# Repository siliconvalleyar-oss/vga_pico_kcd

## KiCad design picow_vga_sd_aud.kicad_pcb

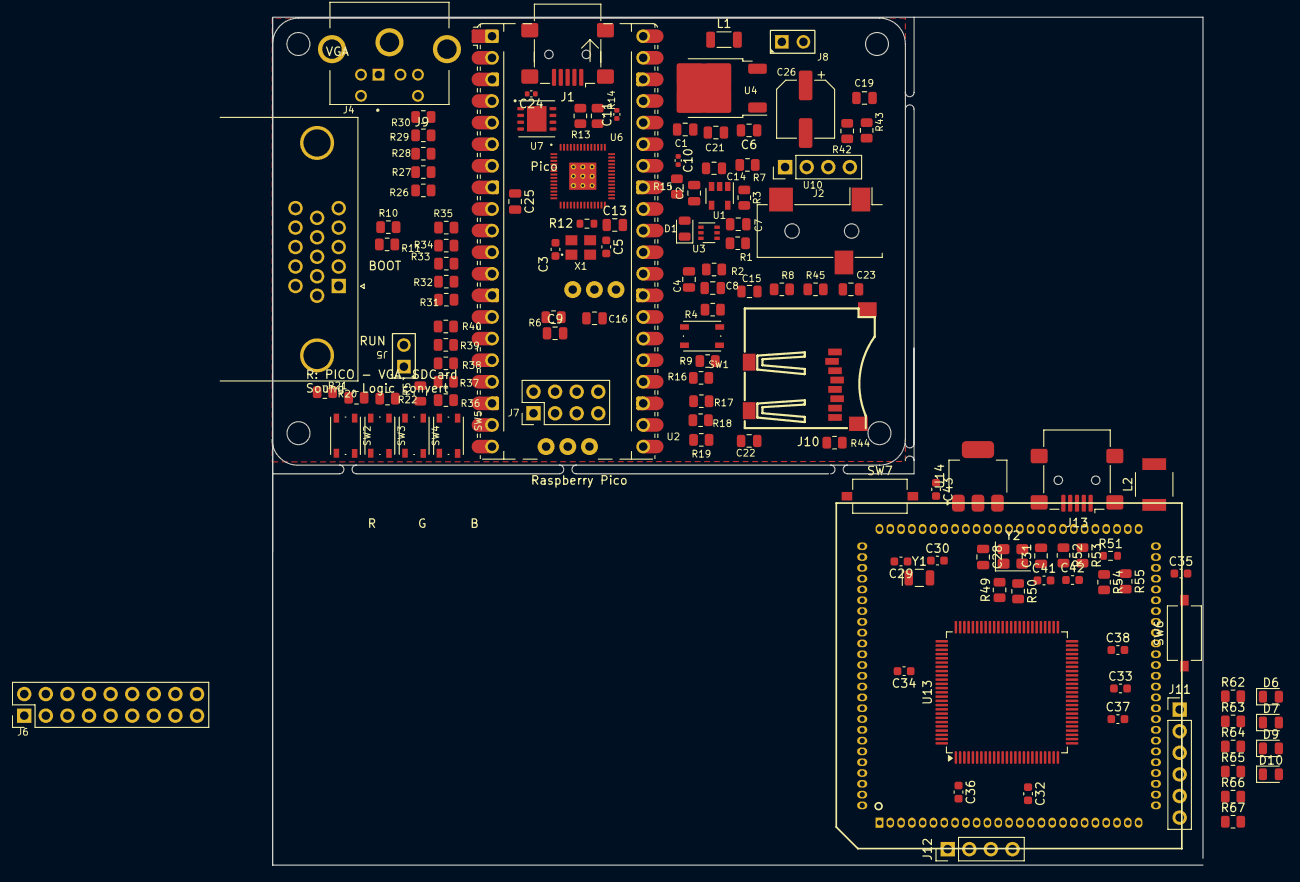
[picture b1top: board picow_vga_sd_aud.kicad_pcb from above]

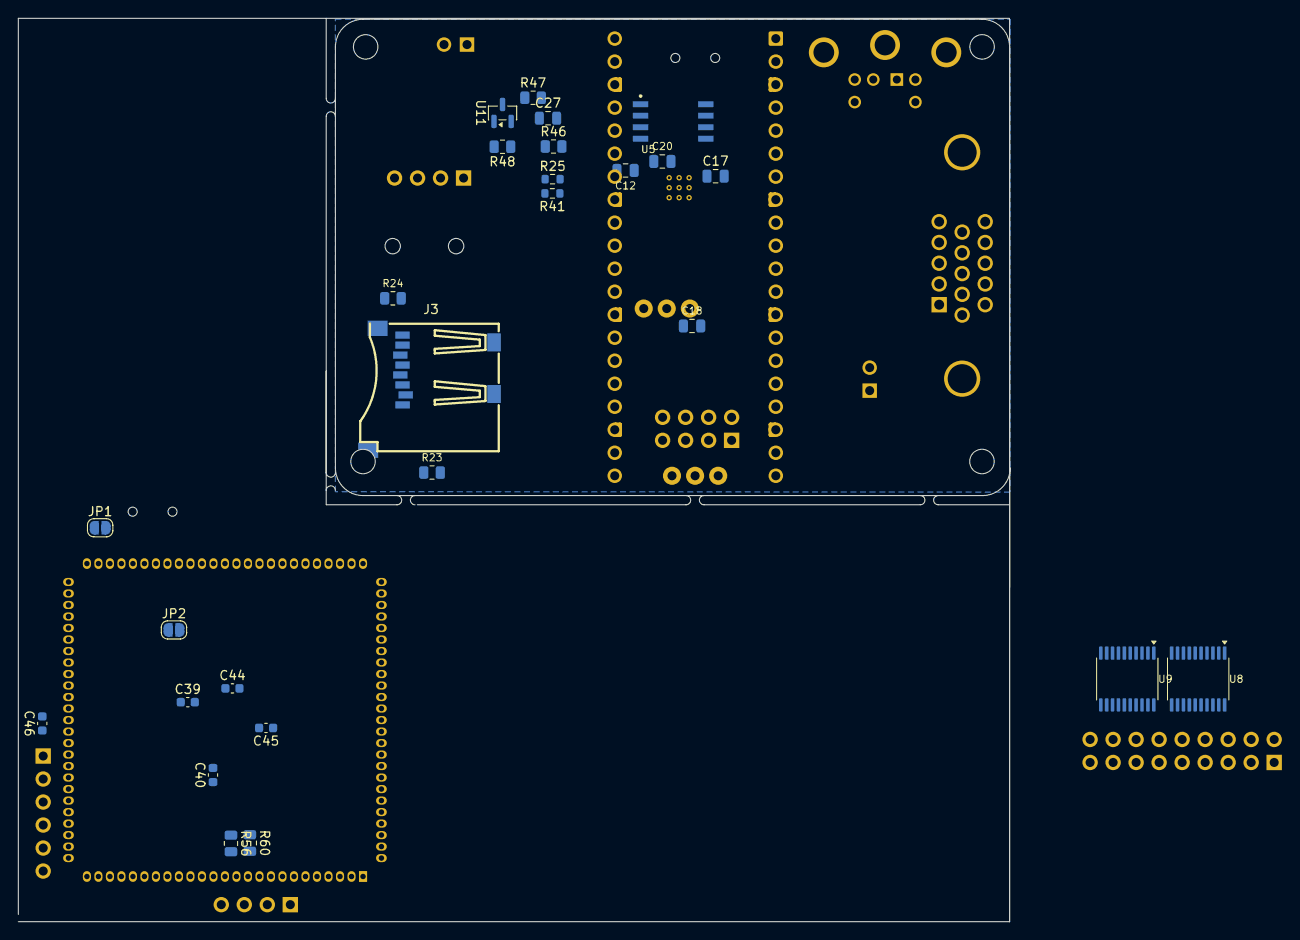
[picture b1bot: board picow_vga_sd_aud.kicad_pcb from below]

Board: 2 copper layers, 109.5 x 99.7 mm, 159 parts (26 on the bottom side), 191 nets, no tracks yet.

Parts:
C1, C2, C13, C17, C27: 1u; C_0805_2012Metric
C3, C5, C29, C30: 15p; C_0603_1608Metric
C4, C7, C8, C12, C16, C18, C20, C21, C22, C23: 100n; C_0805_2012Metric
C6, C9, C19, C25: 10u; C_0805_2012Metric
C10, C11, C24: 100n; C_0402_1005Metric
C14, C15: 47u; C_0805_2012Metric
C26: C_Polarized; CP_Elec_6.3x5.9
C28, C31: 15p; C_0805_2012Metric
C32, C36, C37, C38, C39, C40, C41, C42, C44, C45, C46: 100nf; C_0603_1608Metric
C33, C34: 100; C_0603_1608Metric
C35, C43: 4.7uf; C_0603_1608Metric
D1: LED; LED_0805_2012Metric
D6, D7, D9, D10: LED; D_0805_2012Metric
H1, H2, H3, H4: MountingHole; MountingHole_2.7mm_M2.5
J1: U-M-M5SS-W-2; USB_Mini-B_Lumberg_2486_01_Horizontal
J2: PJ-320BSurface Mount; CUI_SJ-3523-audio-jack
J3, J10: TF-001B
J4: L77HDE15SD1CH4F; DSUB-15-L77HDE15SD1CH4F
J5, J8: TSW-102-07-G-S; samtec_tsw-102-07-g-s
J6: Conn_01x18_Pin; PinHeader_2x09_P2.54mm_Vertical
J7: Conn_02x03_Odd_Even; PinHeader_2x04_P2.54mm_Vertical
J9: Mini-DIN-6; TE_5749180-1
J11: icd; PinHeader_1x06_P2.54mm_Vertical
J12: OLED SSD1306; PinHeader_1x04_P2.54mm_Vertical
J13: USB_A; USB_Mini-B_Lumberg_2486_01_Horizontal
JP1: SolderJumper-2_P1.3mm_Open_RoundedPad1.0x1.5mm
JP2: usb_on; SolderJumper-2_P1.3mm_Open_RoundedPad1.0x1.5mm
L1: 100uH; L_1206_3216Metric
L2: L; L_Neosid_Ms50
R1, R2: 220; R_0805_2012Metric
R3, R4, R54, R55: 100; R_0805_2012Metric
R5, R20, R21, R22, R27, R32, R37, R46, R47, R48: 1k; R_0805_2012Metric
R6, R23, R24: 10k; R_0805_2012Metric
R7, R8, R15: 1.8K; R_0805_2012Metric
R9: DNF; R_0805_2012Metric
R10, R11: 47; R_0805_2012Metric
R12: 1k; R_0603_1608Metric
R13, R14: 27; R_0805_2012Metric
R16, R17, R18, R19, R42, R43, R44, R45, R56, R60, R62, R63, R64, R65, R66, R67: 2k2; R_0805_2012Metric
R25: 10k; R_0603_1608Metric
R26, R31, R36: 499; R_0805_2012Metric
R28, R33, R38: 2k; R_0805_2012Metric
R29, R34, R39: 4.02k; R_0805_2012Metric
R30, R35, R40: 8.06k; R_0805_2012Metric
R41: 1K; R_0603_1608Metric
R49: 1K; R_0805_2012Metric
R50: 1M; R_0805_2012Metric
R51: 0; R_0603_1608Metric
R52, R53: 0; R_0805_2012Metric
SW1, SW2, SW3, SW4, SW5: SKRPACE010; SW_Push_1P1T_NO_Vertical_Wuerth_434133025816
SW6, SW7: K2-1107ST-A4SW-06; SW_Tactile_SPST_NO_Straight_CK_PTS636Sx25SMTRLFS
U1: TLV70033_SOT23-5; SOT-23-5
U2: PicoW; RaspberryPi_Pico
U3: NC7WZ16P6X; SOT-363_SC-70-6
U4: LM1117DT-3.3/NOPB; TO-252-2
U5: W25Q128JVSIQ; generic_soic127p790x195-8
U6: RP2040; rpi_rp2040_vias
U7: W25Q64JVXGIM; Winbond_XSON-8-1EP_4x4mm_P0.8mm_EP2.3x3.0mm
U8, U9: TXS0108; TSSOP-20_4.4x6.5mm_P0.65mm
U10: ER_OLEDM0.91_1x-I2C; PinHeader_1x04_P2.54mm_Vertical
U11: TL431DBZ; SOT-23
U12: PIC32MX795F512L-80x-PF; MA240011_Socket_TQFP100_100pin
U13: PIC32MX795F512L-80I_PF; TQFP-100_14x14mm_P0.5mm
U14: LM1117MDT-3_3_TR; SOT-223-3_TabPin2
X1: 12MHz; generic_xtalcc320x250x80-4
Y1: Crystal_Small; Crystal_SMD_EuroQuartz_EQ161-2Pin_3.2x1.5mm
Y2: 8MHz SMD crystal oscillator ±10ppm ±30ppm SMD3225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; Crystal_SMD_3225-4Pin_3.2x2.5mm

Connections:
+1V1: C11.1, C12.1, C13.1, U6.23 (DVDD), U6.45 (VREG_VOUT), U6.50 (DVDD)
+3.3VA: C2.1, C4.1, U1.5 (OUT), U3.5 (VCC)
+3V: C32.1, C33.1, C36.1, C37.1, C38.1, C39.1, C40.1, C41.1, C43.1, C44.1, C45.1, C46.1, J11.2, JP2.2 (B), U12.2 (VDD), U12.16 (VDD), U12.30 (AVDD), U12.37 (VDD), U12.46 (VDD), U12.55 (VUSB3V3), U12.62 (VDD), U12.86 (VDD), U13.2 (VDD), U13.16 (VDD), U13.37 (VDD), U13.46 (VDD), U13.62 (VDD), U13.86 (VDD), U14.2 (VOUT)
+3V3: C9.1, C10.1, C16.1, C17.1, C18.1, C19.1, C20.1, C21.1, C22.1, C23.1, C24.1, C25.1, C26.1, J3.4 (VDD), J10.4 (VDD), J12.2, R6.1, R16.2, R17.2, R18.2, R19.2, R23.2, R24.2, R25.1, R42.2, R43.2, R44.1, R45.2, R48.1, R56.1, R60.1, SW2.1, SW3.1, SW4.1, U2.36 (3V3), U4.2 (OUT), U5.8 (VCC), U6.1 (IOVDD), U6.10 (IOVDD), U6.22 (IOVDD), U6.33 (IOVDD), U6.42 (IOVDD), U6.43 (ADC_AVDD), U6.44 (VREG_IN), U6.48 (USB_VDD), U6.49 (IOVDD), U7.8 (VCC), U8.1 (VCCA), U9.1 (VCCA), U10.2 (VCC), U13.30 (AVDD)
+5V: C35.2, J13.1 (VBUS), L2.1
/GPIO0: R20.1, R30.2, U2.1 (GPIO0), U6.2 (GPIO0)
/GPIO1: R29.2, U2.2 (GPIO1), U6.3 (GPIO1)
/GPIO2: R28.2, U2.4 (GPIO2), U6.4 (GPIO2)
/GPIO3: R27.2, U2.5 (GPIO3), U6.5 (GPIO3)
/GPIO4: R26.2, U2.6 (GPIO4), U6.6 (GPIO4)
/GPIO5: J3.5 (CLK), J10.2 (DAT3/CD), R9.2, R16.1, U2.7 (GPIO5), U6.7 (GPIO5)
/GPIO6: R21.1, R35.2, U2.9 (GPIO6), U6.8 (GPIO6)
/GPIO7: R34.2, U2.10 (GPIO7), U6.9 (GPIO7)
/GPIO8: R33.2, U2.11 (GPIO8), U6.11 (GPIO8)
/GPIO9: R32.2, U2.12 (GPIO9), U6.12 (GPIO9)
/GPIO10: R31.2, U2.14 (GPIO10), U6.13 (GPIO10)
/GPIO11: R22.1, R40.2, U2.15 (GPIO11), U6.14 (GPIO11)
/GPIO12: R39.2, U2.16 (GPIO12), U6.15 (GPIO12)
/GPIO13: R38.2, U2.17 (GPIO13), U6.16 (GPIO13)
/GPIO14: R37.2, U2.19 (GPIO14), U6.17 (GPIO14)
/GPIO15: R36.2, U2.20 (GPIO15), U6.18 (GPIO15)
/GPIO16: J10.7 (DAT0), R11.2, R19.1, U2.21 (GPIO16), U6.27 (GPIO16)
/GPIO17: R10.2, U2.22 (GPIO17), U6.28 (GPIO17)
/GPIO18: J3.3 (CMD), J10.5 (CLK), R18.1, U2.24 (GPIO18), U6.29 (GPIO18)
/GPIO19: J3.7 (DAT0), J10.3 (CMD), R17.1, U2.25 (GPIO19), U6.30 (GPIO19)
/GPIO20: J7.3, U2.26 (GPIO20), U6.31 (GPIO20)
/GPIO21: J7.1, R42.1, U2.27 (GPIO21), U6.32 (GPIO21), U10.3 (SCL)
/GPIO22: J3.2 (DAT3/CD), R43.1, U2.29 (GPIO22), U6.34 (GPIO22), U10.4 (SDA)
/GPIO25: R15.2, U6.37 (GPIO25)
/GPIO26: J9.1, U2.31 (GPIO26_ADC0), U6.38 (GPIO26_ADC0)
/GPIO27: J9.5, U2.32 (GPIO27_ADC1), U3.3 (A2), U6.39 (GPIO27_ADC1)
/GPIO28: U2.34 (GPIO28_ADC2), U3.1 (A1), U6.40 (GPIO28_ADC2)
/GPIO29: R25.2, R41.1, R46.2, U2.35 (ADC_VREF), U6.41 (GPIO29_ADC3)
/HSYNC: J4.13, R11.1
/PULL_UP2: J10.8 (DAT1), R44.2
/PWM_AUDIO_L: C14.1, J2.2 (T), R7.2
/PWM_AUDIO_R: C15.1, J2.3 (R), R8.2
/PWM_L: R1.2, U3.6 (Y1)
/PWM_LL: C7.1, C14.2, R1.1, R3.2
/PWM_R: R2.2, U3.4 (Y2)
/PWM_RR: C8.1, C15.2, R2.1, R4.2
/RUN: SW1.1, U2.30 (RUN), U6.26 (RUN)
/SD_DAT1: J3.8 (DAT1), J7.4, R24.1
/SD_DAT2: J3.1 (DAT2), J7.2, R23.1
/SWCLK: J7.6, U2.41 (SWCLK), U6.24 (SWCLK)
/SWDIO: J7.5, U2.43 (SWDIO), U6.25 (SWD)
/VGA_B: J4.3, R36.1, R37.1, R38.1, R39.1, R40.1
/VGA_G: J4.2, R31.1, R32.1, R33.1, R34.1, R35.1
/VGA_R: J4.1, R26.1, R27.1, R28.1, R29.1, R30.1
/VSYNC: J4.14, R10.1
/VSYS: C1.1, J8.1, J9.4, U1.1 (IN), U1.3 (EN), U2.39 (VSYS)
/logic_convert/B_1: J6.10, U9.19 (B1)
/logic_convert/B_2: J6.11, U9.18 (B2)
/logic_convert/B_3: J6.12, U9.17 (B3)
/logic_convert/B_4: J6.13, U9.16 (B4)
/logic_convert/B_5: J6.14, U9.15 (B5)
/logic_convert/B_6: J6.15, U9.14 (B6)
/logic_convert/B_7: J6.16, U9.13 (B7)
/logic_convert/B_8: J6.17, U9.12 (B8)
/logic_convert/B_9: J6.2, U8.19 (B1)
/logic_convert/B_10: J6.3, U8.18 (B2)
/logic_convert/B_11: J6.4, U8.17 (B3)
/logic_convert/B_12: J6.5, U8.16 (B4)
/logic_convert/B_13: J6.6, U8.15 (B5)
/logic_convert/B_14: J6.7, U8.14 (B6)
/logic_convert/B_15: J6.8, U8.13 (B7)
/logic_convert/B_16: J6.9, U8.12 (B8)
/logic_convert/D+: J13.3 (D+), R52.1, U12.57 (RG2/D+)
/logic_convert/D-: J13.2 (D-), R53.1, U12.56 (RG3/D-)
/logic_convert/MCLR: J11.1, U12.13 (~MCLR), U13.13 (~MCLR)
/logic_convert/OSC1: C31.1, R50.2, U12.63 (RC12/OSC1/CLK), U13.63 (OSC1/CLKI/RC12), Y2.3
/logic_convert/OSC2: R49.1, U12.64 (RC15/OSC2/CLKO), U13.64 (OSC2/CLKO/RC15)
/logic_convert/PGC: J11.5, U12.26 (PGEC2/RB6), U13.26 (PGEC2/AN6/OCFA/RB6)
/logic_convert/PGD: J11.4, U12.27 (PGED2/RB7), U13.27 (PGED2/AN7/RB7)
/logic_convert/PGM: J11.6, U12.21 (RB4), U13.21 (AN4/C1IN-/CN6/RB4)
/logic_convert/RA0: U12.17 (RA0/TMS), U13.17 (TMS/RA0)
/logic_convert/RA1: U12.38 (RA1/TCK), U13.38 (TCK/RA1)
/logic_convert/RA2: U12.58 (RA2), U13.58 (SCL2/RA2)
/logic_convert/RA3: U12.59 (RA3), U13.59 (SDA2/RA3)
/logic_convert/RA4: U12.60 (RA4/TDI), U13.60 (TDI/RA4)
/logic_convert/RA5: U12.61 (RA5/TDO), U13.61 (TDO/RA5)
/logic_convert/RA6: U12.91 (RA6/TRCLK), U13.91 (TRCLK/RA6)
/logic_convert/RA7: U12.92 (RA7/TRD3), U13.92 (TRD3/RA7)
/logic_convert/RA9: U12.28 (RA9), U13.28 (VREF-/CVREF-/AERXD2/PMA7/RA9)
/logic_convert/RA10: U12.29 (RA10), U13.29 (VREF+/CVREF+/AERXD3/PMA6/RA10)
/logic_convert/RA14: U12.66 (RA14), U13.66 (AETXCLK/SCL1/INT3/RA14)
/logic_convert/RA15: U12.67 (RA15), U13.67 (AETXEN/SDA1/INT4/RA15)
/logic_convert/RB0: U12.25 (PGED1/RB0), U13.25 (PGED1/AN0/CN2/RB0)
/logic_convert/RB1: U12.24 (PGEC1/RB1), U13.24 (PGEC1/AN1/CN3/RB1)
/logic_convert/RB2: U12.23 (RB2), U13.23 (AN2/C2IN-/CN4/RB2)
/logic_convert/RB3: U12.22 (RB3), U13.22 (AN3/C2IN+/CN5/RB3)
/logic_convert/RB5: U12.20 (RB5), U13.20 (AN5/C1IN+/VBUSON/CN7/RB5)
/logic_convert/RB8: U12.32 (RB8), U13.32 (AN8/C1OUT/RB8)
/logic_convert/RB9: U12.33 (RB9), U13.33 (AN9/C2OUT/RB9)
/logic_convert/RB10: U12.34 (RB10), U13.34 (AN10/CVREFOUT/PMA13/RB10)
/logic_convert/RB11: U12.35 (RB11), U13.35 (AN11/ERXERR/AETXERR/PMA12/RB11)
/logic_convert/RB12: U12.41 (RB12), U13.41 (AN12/ERXD0/AECRS/PMA11/RB12)
/logic_convert/RB13: U12.42 (RB13), U13.42 (AN13/ERXD1/AECOL/PMA10/RB13)
/logic_convert/RB14: U12.43 (RB14), U13.43 (AN14/ERXD2/AETXD3/PMALH/PMA1/RB14)
/logic_convert/RB15: U12.44 (RB15), U13.44 (AN15/ERXD3/AETXD2/OCFB/PMALL/PMA0/CN12/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)
/logic_convert/RC1: U12.6 (RC1), U13.6 (T2CK/RC1)
/logic_convert/RC2: U12.7 (RC2), U13.7 (T3CK/AC2TX/RC2)
/logic_convert/RC3: U12.8 (RC3), U13.8 (T4CK/AC2RX/RC3)
/logic_convert/RC4: U12.9 (RC4), U13.9 (T5CK/SDI1/RC4)
/logic_convert/RD0: U12.72 (RD0), U13.72 (SDO1/OC1/INT0/RD0)
/logic_convert/RD1: U12.76 (RD1), U13.76 (OC2/RD1)
/logic_convert/RD2: U12.77 (RD2), U13.77 (OC3/RD2)
/logic_convert/RD3: U12.78 (RD3), U13.78 (OC4/RD3)
/logic_convert/RD4: U12.81 (RD4), U13.81 (OC5/PMWR/CN13/RD4)
/logic_convert/RD5: U12.82 (RD5), U13.82 (PMRD/CN14/RD5)
/logic_convert/RD6: U12.83 (RD6), U13.83 (ETXEN/PMD14/CN15/RD6)
/logic_convert/RD7: U12.84 (RD7), U13.84 (ETXCLK/PMD15/CN16/RD7)
/logic_convert/RD8: U12.68 (RD8), U13.68 (RTCC/EMDIO/AEMDIO/IC1/RD8)
/logic_convert/RD9: U12.69 (RD9), U13.69 (~SS1/IC2/RD9)
/logic_convert/RD10: U12.70 (RD10), U13.70 (SCK1/IC3/PMCS2/PMA15/RD10)
/logic_convert/RD11: U12.71 (RD11), U13.71 (EMDC/AEMDC/IC4/PMCS1/PMA14/RD11)
/logic_convert/RD12: U12.79 (RD12), U13.79 (ETXD2/IC5/PMD12/RD12)
/logic_convert/RD13: U12.80 (RD13), U13.80 (ETXD3/PMD13/CN19/RD13)
/logic_convert/RD14: U12.47 (RD14), U13.47 (AETXD0/~SS3/U4RX/~U1CTS/CN20/RD14)
/logic_convert/RD15: U12.48 (RD15), U13.48 (AETXD1/SCK3/U4TX/~U1RTS/CN21/RD15)
/logic_convert/RE0: U12.93 (RE0), U13.93 (PMD0/RE0)
/logic_convert/RE1: U12.94 (RE1), U13.94 (PMD1/RE1)
/logic_convert/RE2: U12.98 (RE2), U13.98 (PMD2/RE2)
/logic_convert/RE3: U12.99 (RE3), U13.99 (PMD3/RE3)
/logic_convert/RE4: U12.100 (RE4), U13.100 (PMD4/RE4)
/logic_convert/RE5: U12.3 (RE5), U13.3 (PMD5/RE5)
/logic_convert/RE6: U12.4 (RE6), U13.4 (PMD6/RE6)
/logic_convert/RE7: U12.5 (RE7), U13.5 (PMD7/RE7)
/logic_convert/RE8: U12.18 (RE8), U13.18 (AERXD0/INT1/RE8)
/logic_convert/RE9: U12.19 (RE9), U13.19 (AERXD1/INT2/RE9)
/logic_convert/RF0: U12.87 (RF0), U13.87 (C1RX/ETXD1/PMD11/RF0)
/logic_convert/RF1: U12.88 (RF1), U13.88 (C1TX/ETXD0/PMD10/RF1)
/logic_convert/RF2: R55.2, U12.52 (RF2), U13.52 (SDA3/SDI3/U1RX/RF2)
/logic_convert/RF3: U12.51 (RF3), U13.51 (USBID/RF3)
/logic_convert/RF4: U12.49 (RF4), U13.49 (SDA5/SDI4/U2RX/PMA9/CN17/RF4)
/logic_convert/RF5: U12.50 (RF5), U13.50 (SCL5/SDO4/U2TX/PMA8/CN18/RF5)
/logic_convert/RF8: R54.2, U12.53 (RF8), U13.53 (SCL3/SDO3/U1TX/RF8)
/logic_convert/RF12: U12.40 (RF12), U13.40 (AC1RX/~SS4/U5RX/~U2CTS/RF12)
/logic_convert/RF13: U12.39 (RF13), U13.39 (AC1TX/SCK4/U5TX/~U2RTS/RF13)
/logic_convert/RG0: U12.90 (RG0), U13.90 (C2RX/PMD8/RG0)
/logic_convert/RG1: U12.89 (RG1), U13.89 (C2TX/ETXERR/PMD9/RG1)
/logic_convert/RG6: U12.10 (RG6), U13.10 (ECOL/SCK2/U6TX/~U3RTS/PMA5/CN8/RG6)
/logic_convert/RG7: J12.4, R60.2, U12.11 (RG7), U13.11 (ECRS/SDA4/SDI2/U3RX/PMA4/CN9/RG7)
/logic_convert/RG8: J12.3, R56.2, U12.12 (RG8), U13.12 (ERXDV/AERXDV/ECRSDV/AECRSDV/SCL4/SDO2/U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)
/logic_convert/RG9: U12.14 (RG9), U13.14 (ERXCLK/AERXCLK/EREFCLK/AEREFCLK/~SS2/U6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)
/logic_convert/RG12: U12.96 (RG12/TRD1), U13.96 (TRD1/RG12)
/logic_convert/RG13: U12.97 (RG13/TRD0), U13.97 (TRD0/RG13)
/logic_convert/RG14: U12.95 (RG14/TRD2), U13.95 (TRD2/RG14)
/logic_convert/RG15: U12.1 (RG15), U13.1 (AERXERR/RG15)
/logic_convert/VBUS_: R51.1, U12.54 (VBUS), U13.54 (VBUS)
/logic_convert/VDD_CORE: C34.1, U12.85 (VCAP/VDDCORE), U13.85 (VCAP/VDDCORE)
/logic_convert/VUSB3V3: C42.1, JP2.1 (A), U13.55 (VUSB3V3)
/logic_convert/osc_1: C30.1, U12.73 (RC13/SOSCI), U13.73 (SOSCI/CN1/RC13), Y1.2
/logic_convert/osc_2: C29.1, U12.74 (RC14/SOSCO), U13.74 (SOSCO/T1CK/CN0/RC14), Y1.1
/pico/QSPI_SCLK: U5.6 (CLK), U6.52 (QSPI_SCLK), U7.6 (CLK)
/pico/QSPI_SD0: U5.5 (DI_IO0), U6.53 (QSPI_SD0), U7.5 (DI_IO0)
/pico/QSPI_SD1: U5.2 (DO_IO1), U6.55 (QSPI_SD1), U7.2 (DO_IO1)
/pico/QSPI_SD2: U5.3 (~WP_IO2), U6.54 (QSPI_SD2), U7.3 (~WP_IO2)
/pico/QSPI_SD3: U5.7 (~HOLD_IO3), U6.51 (QSPI_SD3), U7.7 (~HOLD_IO3)
/pico/QSPI_SS: R5.1, R6.2, U5.1 (~CS), U6.56 (QSPI_~SS), U7.1 (~CS)
/pico/USB_D+: J1.3 (D+), R13.1
/pico/USB_D-: J1.2 (D-), R14.1
/pico/U_D+: R13.2, U6.47 (USB_DP)
/pico/U_D-: R14.2, U6.46 (USB_DM)
/pico/XIN: C3.1, U6.20 (XIN), X1.1
/pico/XOUT: R12.2, U6.21 (XOUT)
/pico/~USB_BOOT: J5.1, R5.2, SW5.1
GND: C1.2, C2.2, C3.2, C4.2, C5.2, C6.2, C7.2, C8.2, C9.2, C10.2, C11.2, C12.2, C13.2, C16.2, C17.2, C18.2, C19.2, C20.2, C21.2, C22.2, C23.2, C24.2, C25.2, C26.2, C27.2, C28.2, C29.2, C30.2, C31.2, C32.2, C33.2, C34.2, C35.1, C36.2, C37.2, C38.2, C39.2, C40.2, C41.2, C42.2, C43.2, C44.2, C45.2, C46.2, D1.1 (K), J1.5 (GND), J2.1 (S), J3.6 (VSS), J3.11 (SHIELD), J4.0, J4.5, J4.6, J4.7, J4.8, J4.10, J5.2, J6.1, J6.18, J7.7, J7.8, J8.2, J9.3, J10.6 (VSS), J11.3, J12.1, J13.4 (GND), JP1.2 (B), R3.1, R4.1, R7.1, R8.1, R9.1, R41.2, SW1.2, SW5.2, SW6.2, SW7.2, U1.2 (GND), U2.3 (GND), U2.8 (GND), U2.13 (GND), U2.18 (GND), U2.23 (GND), U2.28 (GND), U2.33 (AGND), U2.38 (GND), U2.42 (GND), U3.2 (GND), U4.1 (GND), U5.4 (GND), U6.19 (TESTEN), U6.57 (GND), U7.4 (GND), U8.11 (GND), U9.11 (GND), U10.1 (GND), U11.3 (A), U12.15 (VSS), U12.31 (AVSS), U12.36 (VSS), U12.45 (VSS), U12.65 (VSS), U12.75 (VSS), U13.15 (VSS), U13.31 (AVSS), U13.36 (VSS), U13.45 (VSS), U13.65 (VSS), U13.75 (VSS), U14.1 (GND), X1.2, X1.4, Y2.2, Y2.4
unnamed: C5.1, R12.1, X1.3
unnamed: C27.1, R46.1, R47.2
unnamed: C28.1, R49.2, R50.1, Y2.1
unnamed: D1.2 (A), R15.1
unnamed: D6.2 (A), R66.1
unnamed: D7.2 (A), R67.1
unnamed: D9.2 (A), R64.1
unnamed: D10.2 (A), R65.1
unnamed: D6.1 (K), D7.1 (K), D9.1 (K), D10.1 (K)
unnamed: J10.1 (DAT2), R45.1
unnamed: J13.SH (Shield), JP1.1 (A)
unnamed: R20.2, SW2.2
unnamed: R21.2, SW3.2
unnamed: R22.2, SW4.2
unnamed: R62.1, SW7.1
unnamed: R63.1, SW6.1
unnamed: C6.1, L1.2, U4.3 (IN)
unnamed: R48.2, U11.1 (K)
unnamed: R47.1, U11.2 (REF)
unnamed: R52.2, U13.57 (D+/RG2)
unnamed: R53.2, U13.56 (D-/RG3)
unnamed: L2.2, U14.3 (VIN)
VBUS: J1.1 (VCC), L1.1, U2.40 (VBUS), U8.10 (OE), U8.20 (VCCB), U9.10 (OE), U9.20 (VCCB)

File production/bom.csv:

Designator,Footprint,Quantity,Value,LCSC Part #
"C1, C13, C17, C2",0805,4,1u,C1779
"C10, C11, C24",0402,3,100n,C1525
"C12, C16, C20, C21, C22, C23, C4, C7, C8",0805,9,100n,C28233
"C14, C15",0805,2,47u,
"C19, C25, C6, C9",0805,4,10u,C15850
C26,CP_Elec_6.3x5.9,1,C_Polarized,
"C3, C5",0603,2,15p,C107110 
D1,0805,1,LED,C2297
J1,USB_Mini-B_Lumberg_2486_01_Horizontal,1,10103594-0001LF,
J10,3M_2908-05WB-MG,1,Micro_SD_Card,C125617
J2,CUI_SJ-3523-audio-jack,1,AudioJack3,
J4,DSUB-15-L77HDE15SD1CH4F,1,L77HDE15SD1CH4F,
J8,samtec_tsw-102-07-g-s,1,TSW-102-07-G-S,
J9,TE_5749180-1,1,Mini-DIN-6,
L1,1206,1,100uH,C74489
"R1, R2",0805,2,220,
"R10, R11",0805,2,47,C17477
R12,0603,1,1k,C17513
"R13, R14",0805,2,27,C2933393
"R15, R7, R8",0805,3,1.8K,
"R16, R17, R18, R19, R42, R43, R44, R45",0805,8,2k2,C17520
"R20, R21, R22, R27, R32, R37, R5",0805,7,1k,C17673
"R26, R31, R36",0805,3,499,
"R28, R33, R38",0805,3,2k,
"R29, R34, R39",0805,3,4.02k,
"R3, R4",0805,2,100,
"R30, R35, R40",0805,3,8.06k,
SW1,SW_Push_1P1T_NO_Vertical_Wuerth_434133025816,1,SW_Push,C92584
SW2,SW_Push_1P1T_NO_Vertical_Wuerth_434133025816,1,SW_Push,
"SW3, SW4",SW_Push_1P1T_NO_Vertical_Wuerth_434133025816,2,SW_Push,C83916
SW5,SW_Push_1P1T_NO_Vertical_Wuerth_434133025816,1,SW_boot,
U1,SOT-23-5,1,TLV70033_SOT23-5,C5366877
U3,SOT-363_SC-70-6,1,NC7WZ16P6X,
U4,TO-252-2,1,NCP1117ST33T3G,
U7,Winbond_XSON-8-1EP_4x4mm_P0.8mm_EP2.3x3.0mm,1,W25Q128JVSIQ,
X1,generic_xtalcc320x250x80-4,1,12MHz,
